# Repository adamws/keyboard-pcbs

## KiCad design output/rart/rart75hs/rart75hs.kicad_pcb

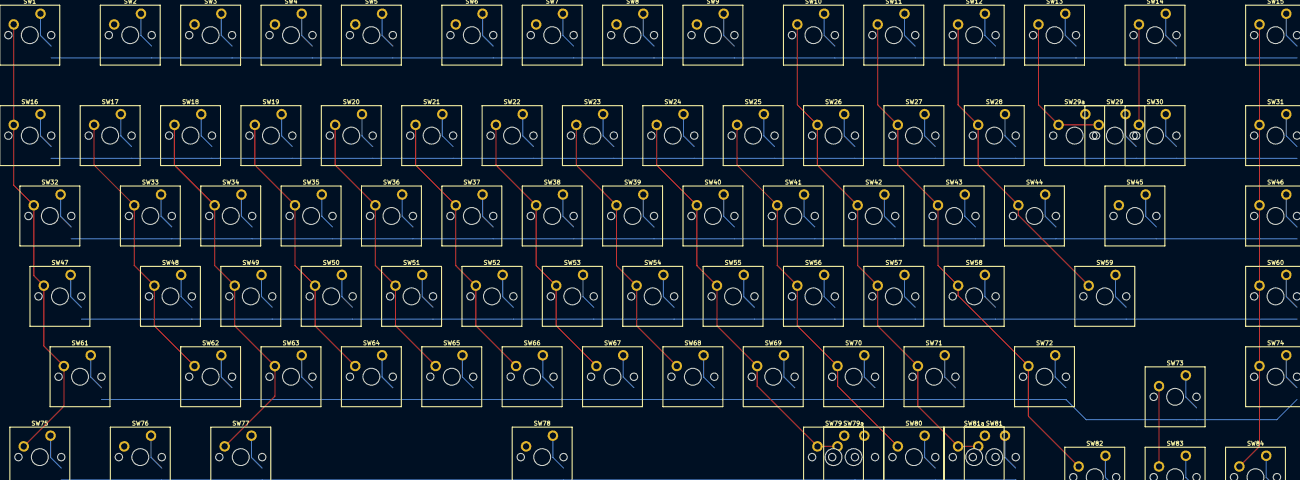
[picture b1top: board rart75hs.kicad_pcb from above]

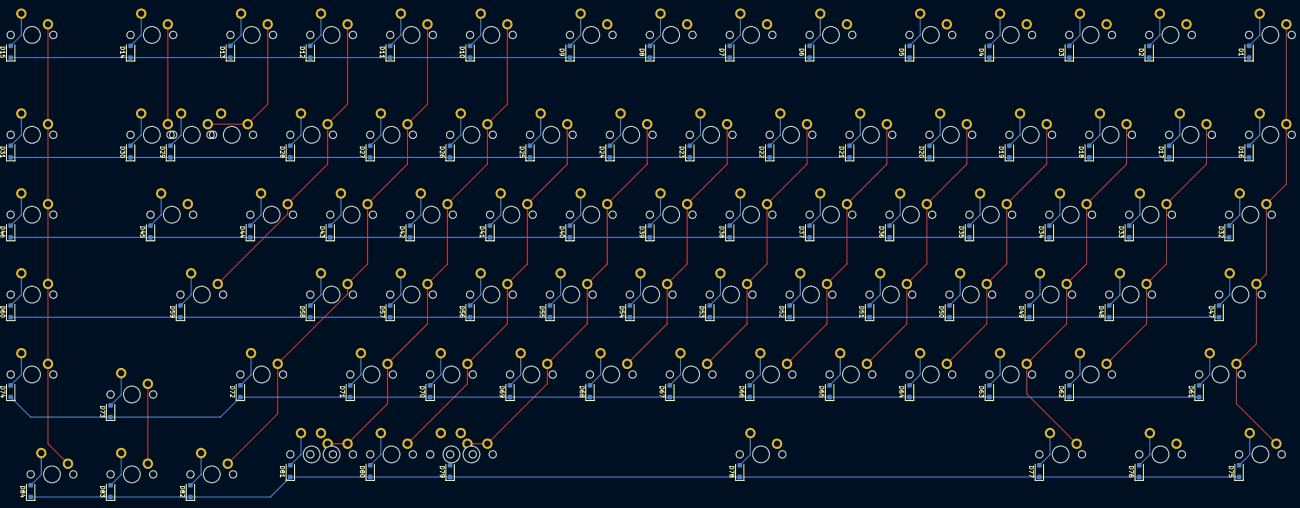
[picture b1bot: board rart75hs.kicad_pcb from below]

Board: 2 copper layers, 171 parts (84 on the bottom side), 106 nets.

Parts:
D1, D2, D3, D4, D5, D6, D7, D8, D9, D10, D11, D12, D13, D14, D15, D16, D17, D18, D19, D20, D21, D22, D23, D24, D25, D26, D27, D28, D29, D30, D31, D32, D33, D34, D35, D36, D37, D38, D39, D40, D41, D42, D43, D44, D45, D46, D47, D48, D49, D50, D51, D52, D53, D54, D55, D56, D57, D58, D59, D60, D61, D62, D63, D64, D65, D66, D67, D68, D69, D70, D71, D72, D73, D74, D75, D76, D77, D78, D79, D80, D81, D82, D83, D84: D_SOD-123F
SW1, SW2, SW3, SW4, SW5, SW6, SW7, SW8, SW9, SW10, SW11, SW12, SW13, SW14, SW15, SW16, SW17, SW18, SW19, SW20, SW21, SW22, SW23, SW24, SW25, SW26, SW27, SW28, SW29, SW29a, SW30, SW31, SW32, SW33, SW34, SW35, SW36, SW37, SW38, SW39, SW40, SW41, SW42, SW43, SW44, SW45, SW46, SW47, SW48, SW49, SW50, SW51, SW52, SW53, SW54, SW55, SW56, SW57, SW58, SW59, SW60, SW61, SW62, SW63, SW64, SW65, SW66, SW67, SW68, SW69, SW70, SW71, SW72, SW73, SW74, SW75, SW76, SW77, SW78, SW79, SW79a, SW80, SW81, SW81a, SW82, SW83, SW84: SW_Cherry_MX_PCB_1.00u

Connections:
COL0: SW1.1, SW16.1, SW32.1, SW47.1, SW61.1, SW75.1
COL1: SW2.1, SW17.1, SW33.1, SW48.1, SW62.1, SW76.1
COL2: SW3.1, SW18.1, SW34.1, SW49.1, SW63.1, SW77.1
COL3: SW4.1, SW19.1, SW35.1, SW50.1, SW64.1
COL4: SW5.1, SW20.1, SW36.1, SW51.1, SW65.1, SW78.1
COL5: SW6.1, SW21.1, SW37.1, SW52.1, SW66.1
COL6: SW7.1, SW22.1, SW38.1, SW53.1, SW67.1
COL7: SW8.1, SW23.1, SW39.1, SW54.1, SW68.1
COL8: SW9.1, SW24.1, SW40.1, SW55.1, SW69.1, SW79.1, SW79a.1
COL9: SW25.1, SW41.1, SW56.1, SW70.1, SW80.1
COL10: SW10.1, SW26.1, SW42.1, SW57.1, SW71.1, SW81.1, SW81a.1
COL11: SW11.1, SW27.1, SW43.1, SW58.1, SW72.1, SW82.1
COL12: SW12.1, SW28.1, SW44.1, SW59.1
COL13: SW13.1, SW29.1, SW29a.1, SW45.1
COL14: SW14.1, SW30.1, SW73.1, SW83.1
COL15: SW15.1, SW31.1, SW46.1, SW60.1, SW74.1, SW84.1
unnamed: D1.2, SW1.2
unnamed: D2.2, SW2.2
unnamed: D3.2, SW3.2
unnamed: D4.2, SW4.2
unnamed: D5.2, SW5.2
unnamed: D6.2, SW6.2
unnamed: D7.2, SW7.2
unnamed: D8.2, SW8.2
unnamed: D9.2, SW9.2
unnamed: D10.2, SW10.2
unnamed: D11.2, SW11.2
unnamed: D12.2, SW12.2
unnamed: D13.2, SW13.2
unnamed: D14.2, SW14.2
unnamed: D15.2, SW15.2
unnamed: D16.2, SW16.2
unnamed: D17.2, SW17.2
unnamed: D18.2, SW18.2
unnamed: D19.2, SW19.2
unnamed: D20.2, SW20.2
unnamed: D21.2, SW21.2
unnamed: D22.2, SW22.2
unnamed: D23.2, SW23.2
unnamed: D24.2, SW24.2
unnamed: D25.2, SW25.2
unnamed: D26.2, SW26.2
unnamed: D27.2, SW27.2
unnamed: D28.2, SW28.2
unnamed: D29.2, SW29.2, SW29a.2
unnamed: D30.2, SW30.2
unnamed: D31.2, SW31.2
unnamed: D32.2, SW32.2
unnamed: D33.2, SW33.2
unnamed: D34.2, SW34.2
unnamed: D35.2, SW35.2
unnamed: D36.2, SW36.2
unnamed: D37.2, SW37.2
unnamed: D38.2, SW38.2
unnamed: D39.2, SW39.2
unnamed: D40.2, SW40.2
unnamed: D41.2, SW41.2
unnamed: D42.2, SW42.2
unnamed: D43.2, SW43.2
unnamed: D44.2, SW44.2
unnamed: D45.2, SW45.2
unnamed: D46.2, SW46.2
unnamed: D47.2, SW47.2
unnamed: D48.2, SW48.2
unnamed: D49.2, SW49.2
unnamed: D50.2, SW50.2
unnamed: D51.2, SW51.2
unnamed: D52.2, SW52.2
unnamed: D53.2, SW53.2
unnamed: D54.2, SW54.2
unnamed: D55.2, SW55.2
unnamed: D56.2, SW56.2
unnamed: D57.2, SW57.2
unnamed: D58.2, SW58.2
unnamed: D59.2, SW59.2
unnamed: D60.2, SW60.2
unnamed: D61.2, SW61.2
unnamed: D62.2, SW62.2
unnamed: D63.2, SW63.2
unnamed: D64.2, SW64.2
unnamed: D65.2, SW65.2
unnamed: D66.2, SW66.2
unnamed: D67.2, SW67.2
unnamed: D68.2, SW68.2
unnamed: D69.2, SW69.2
unnamed: D70.2, SW70.2
unnamed: D71.2, SW71.2
unnamed: D72.2, SW72.2
unnamed: D73.2, SW73.2
unnamed: D74.2, SW74.2
unnamed: D75.2, SW75.2
unnamed: D76.2, SW76.2
unnamed: D77.2, SW77.2
unnamed: D78.2, SW78.2
unnamed: D79.2, SW79.2, SW79a.2
unnamed: D80.2, SW80.2
unnamed: D81.2, SW81.2, SW81a.2
unnamed: D82.2, SW82.2
unnamed: D83.2, SW83.2
unnamed: D84.2, SW84.2
ROW0: D1.1, D2.1, D3.1, D4.1, D5.1, D6.1, D7.1, D8.1, D9.1, D10.1, D11.1, D12.1, D13.1, D14.1, D15.1
ROW1: D16.1, D17.1, D18.1, D19.1, D20.1, D21.1, D22.1, D23.1, D24.1, D25.1, D26.1, D27.1, D28.1, D29.1, D30.1, D31.1
ROW2: D32.1, D33.1, D34.1, D35.1, D36.1, D37.1, D38.1, D39.1, D40.1, D41.1, D42.1, D43.1, D44.1, D45.1, D46.1
ROW3: D47.1, D48.1, D49.1, D50.1, D51.1, D52.1, D53.1, D54.1, D55.1, D56.1, D57.1, D58.1, D59.1, D60.1
ROW4: D61.1, D62.1, D63.1, D64.1, D65.1, D66.1, D67.1, D68.1, D69.1, D70.1, D71.1, D72.1, D73.1, D74.1
ROW5: D75.1, D76.1, D77.1, D78.1, D79.1, D80.1, D81.1, D82.1, D83.1, D84.1

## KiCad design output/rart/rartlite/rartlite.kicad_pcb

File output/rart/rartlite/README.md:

## rart/rartlite

[layout](rartlite-kle.json) - [PCB](rartlite.kicad_pcb)

{:loading="lazy"}

[Open in keyboard-layout-editor](http://www.keyboard-layout-editor.com/##@@=0,0%0A%0A%0A0,0&=1,0%0A%0A%0A0,0&=0,1%0A%0A%0A0,0&=1,1%0A%0A%0A0,0&=0,2%0A%0A%0A0,0&=1,2%0A%0A%0A0,0&=0,3%0A%0A%0A0,0&=1,3%0A%0A%0A0,0&=0,4%0A%0A%0A0,0&=1,4%0A%0A%0A0,0&=3,4%0A%0A%0A0,0&=0,5%0A%0A%0A0,0&_x:0.25;&=1,5%0A%0A%0A0,0&=0,6%0A%0A%0A0,0&=1,6%0A%0A%0A0,0;&@_w:1.5;&=2,0%0A%0A%0A0,0&=3,0%0A%0A%0A0,0&=2,1%0A%0A%0A0,0&=3,1%0A%0A%0A0,0&=2,2%0A%0A%0A0,0&=3,2%0A%0A%0A0,0&=2,3%0A%0A%0A0,0&=3,3%0A%0A%0A0,0&=2,4%0A%0A%0A0,0&=5,4%0A%0A%0A0,0&_w:1.5;&=2,5%0A%0A%0A0,0&_x:0.25;&=3,5%0A%0A%0A0,0&=2,6%0A%0A%0A0,0&=3,6%0A%0A%0A0,0;&@_w:1.75;&=4,0%0A%0A%0A0,0&=5,0%0A%0A%0A0,0&=4,1%0A%0A%0A0,0&=5,1%0A%0A%0A0,0&=4,2%0A%0A%0A0,0&=5,2%0A%0A%0A0,0&=4,3%0A%0A%0A0,0&=5,3%0A%0A%0A0,0&=4,4%0A%0A%0A0,0&=7,4%0A%0A%0A0,0&_x:1.5;&=5,5%0A%0A%0A0,0&=4,6%0A%0A%0A0,0&=5,6%0A%0A%0A0,0;&@_x:11&y:-0.75;&=4,5%0A%0A%0A0,0;&@_y:-0.25&w:1.25;&=6,0%0A%0A%0A0,0&=7,0%0A%0A%0A0,0&_w:2.25;&=6,1%0A%0A%0A0,0&_w:1.25;&=6,2%0A%0A%0A0,0&_w:2.75;&=6,3%0A%0A%0A0,0&_w:1.25;&=7,3%0A%0A%0A0,0&_x:3.5;&=6,6%0A%0A%0A0,0&=7,6%0A%0A%0A0,0;&@_x:10&y:-0.75;&=6,4%0A%0A%0A0,0&=6,5%0A%0A%0A0,0&=7,5%0A%0A%0A0,0;&@=0,0%0A%0A%0A0,1&=1,0%0A%0A%0A0,1&=0,1%0A%0A%0A0,1&=1,1%0A%0A%0A0,1&=0,2%0A%0A%0A0,1&=1,2%0A%0A%0A0,1&=0,3%0A%0A%0A0,1&=1,3%0A%0A%0A0,1&=0,4%0A%0A%0A0,1&=1,4%0A%0A%0A0,1&=3,4%0A%0A%0A0,1&=0,5%0A%0A%0A0,1&_x:0.25;&=1,5%0A%0A%0A0,1&=0,6%0A%0A%0A0,1&=1,6%0A%0A%0A0,1;&@_w:1.5;&=2,0%0A%0A%0A0,1&=3,0%0A%0A%0A0,1&=2,1%0A%0A%0A0,1&=3,1%0A%0A%0A0,1&=2,2%0A%0A%0A0,1&=3,2%0A%0A%0A0,1&=2,3%0A%0A%0A0,1&=3,3%0A%0A%0A0,1&=2,4%0A%0A%0A0,1&=5,4%0A%0A%0A0,1&_w:1.5;&=2,5%0A%0A%0A0,1&_x:0.25;&=3,5%0A%0A%0A0,1&=2,6%0A%0A%0A0,1&=3,6%0A%0A%0A0,1;&@_w:1.75;&=4,0%0A%0A%0A0,1&=5,0%0A%0A%0A0,1&=4,1%0A%0A%0A0,1&=5,1%0A%0A%0A0,1&=4,2%0A%0A%0A0,1&=5,2%0A%0A%0A0,1&=4,3%0A%0A%0A0,1&=5,3%0A%0A%0A0,1&=4,4%0A%0A%0A0,1&=7,4%0A%0A%0A0,1&_x:1.5;&=5,5%0A%0A%0A0,1&=4,6%0A%0A%0A0,1&=5,6%0A%0A%0A0,1;&@_x:11&y:-0.75;&=4,5%0A%0A%0A0,1;&@_y:-0.25&w:1.25;&=6,0%0A%0A%0A0,1&=7,0%0A%0A%0A0,1&_w:6.25;&=6,2%0A%0A%0A0,1&_w:1.25;&=7,3%0A%0A%0A0,1&_x:3.5;&=6,6%0A%0A%0A0,1&=7,6%0A%0A%0A0,1;&@_x:10&y:-0.75;&=6,4%0A%0A%0A0,1&=6,5%0A%0A%0A0,1&=7,5%0A%0A%0A0,1;&@=1,6%0A%0A%0A0,2&=0,6%0A%0A%0A0,2&=1,5%0A%0A%0A0,2&_x:0.25;&=0,5%0A%0A%0A0,2&=3,4%0A%0A%0A0,2&=1,4%0A%0A%0A0,2&=0,4%0A%0A%0A0,2&=1,3%0A%0A%0A0,2&=0,3%0A%0A%0A0,2&=1,2%0A%0A%0A0,2&=0,2%0A%0A%0A0,2&=1,1%0A%0A%0A0,2&=0,1%0A%0A%0A0,2&=1,0%0A%0A%0A0,2&=0,0%0A%0A%0A0,2;&@=3,6%0A%0A%0A0,2&=2,6%0A%0A%0A0,2&=3,5%0A%0A%0A0,2&_x:0.25&w:1.5;&=2,5%0A%0A%0A0,2&=5,4%0A%0A%0A0,2&=2,4%0A%0A%0A0,2&=3,3%0A%0A%0A0,2&=2,3%0A%0A%0A0,2&=3,2%0A%0A%0A0,2&=2,2%0A%0A%0A0,2&=3,1%0A%0A%0A0,2&=2,1%0A%0A%0A0,2&=3,0%0A%0A%0A0,2&_w:1.5;&=2,0%0A%0A%0A0,2;&@=5,6%0A%0A%0A0,2&=4,6%0A%0A%0A0,2&=5,5%0A%0A%0A0,2&_x:1.5;&=7,4%0A%0A%0A0,2&=4,4%0A%0A%0A0,2&=5,3%0A%0A%0A0,2&=4,3%0A%0A%0A0,2&=5,2%0A%0A%0A0,2&=4,2%0A%0A%0A0,2&=5,1%0A%0A%0A0,2&=4,1%0A%0A%0A0,2&=5,0%0A%0A%0A0,2&_w:1.75;&=4,0%0A%0A%0A0,2;&@_x:3.25&y:-0.75;&=4,5%0A%0A%0A0,2;&@_y:-0.25;&=7,6%0A%0A%0A0,2&=6,6%0A%0A%0A0,2&_x:3.5&w:1.25;&=7,3%0A%0A%0A0,2&_w:2.75;&=6,3%0A%0A%0A0,2&_w:1.25;&=6,2%0A%0A%0A0,2&_w:2.25;&=6,1%0A%0A%0A0,2&=7,0%0A%0A%0A0,2&_w:1.25;&=6,0%0A%0A%0A0,2;&@_x:2.25&y:-0.75;&=7,5%0A%0A%0A0,2&=6,5%0A%0A%0A0,2&=6,4%0A%0A%0A0,2;&@=1,6%0A%0A%0A0,3&=0,6%0A%0A%0A0,3&=1,5%0A%0A%0A0,3&_x:0.25;&=0,5%0A%0A%0A0,3&=3,4%0A%0A%0A0,3&=1,4%0A%0A%0A0,3&=0,4%0A%0A%0A0,3&=1,3%0A%0A%0A0,3&=0,3%0A%0A%0A0,3&=1,2%0A%0A%0A0,3&=0,2%0A%0A%0A0,3&=1,1%0A%0A%0A0,3&=0,1%0A%0A%0A0,3&=1,0%0A%0A%0A0,3&=0,0%0A%0A%0A0,3;&@=3,6%0A%0A%0A0,3&=2,6%0A%0A%0A0,3&=3,5%0A%0A%0A0,3&_x:0.25&w:1.5;&=2,5%0A%0A%0A0,3&=5,4%0A%0A%0A0,3&=2,4%0A%0A%0A0,3&=3,3%0A%0A%0A0,3&=2,3%0A%0A%0A0,3&=3,2%0A%0A%0A0,3&=2,2%0A%0A%0A0,3&=3,1%0A%0A%0A0,3&=2,1%0A%0A%0A0,3&=3,0%0A%0A%0A0,3&_w:1.5;&=2,0%0A%0A%0A0,3;&@=5,6%0A%0A%0A0,3&=4,6%0A%0A%0A0,3&=5,5%0A%0A%0A0,3&_x:1.5;&=7,4%0A%0A%0A0,3&=4,4%0A%0A%0A0,3&=5,3%0A%0A%0A0,3&=4,3%0A%0A%0A0,3&=5,2%0A%0A%0A0,3&=4,2%0A%0A%0A0,3&=5,1%0A%0A%0A0,3&=4,1%0A%0A%0A0,3&=5,0%0A%0A%0A0,3&_w:1.75;&=4,0%0A%0A%0A0,3;&@_x:3.25&y:-0.75;&=4,5%0A%0A%0A0,3;&@_y:-0.25;&=7,6%0A%0A%0A0,3&=6,6%0A%0A%0A0,3&_x:3.5&w:1.25;&=7,3%0A%0A%0A0,3&_w:6.25;&=6,2%0A%0A%0A0,3&=7,0%0A%0A%0A0,3&_w:1.25;&=6,0%0A%0A%0A0,3;&@_x:2.25&y:-0.75;&=7,5%0A%0A%0A0,3&=6,5%0A%0A%0A0,3&=6,4%0A%0A%0A0,3)

{:loading="lazy"}

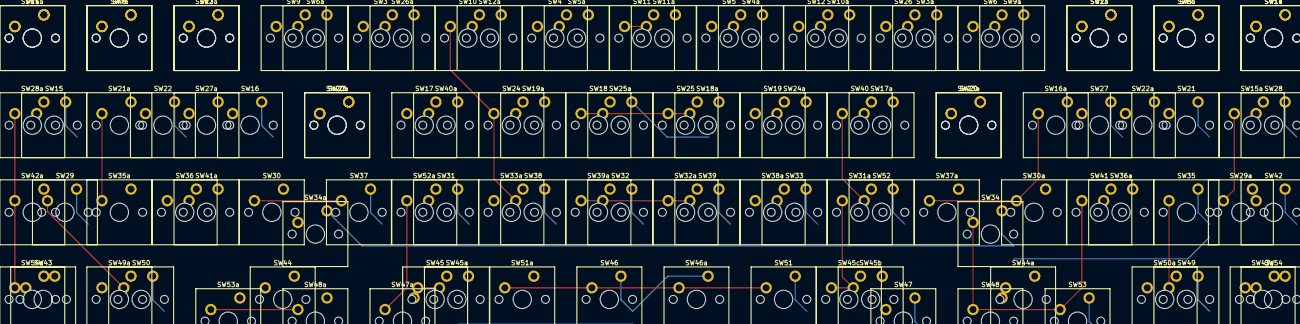
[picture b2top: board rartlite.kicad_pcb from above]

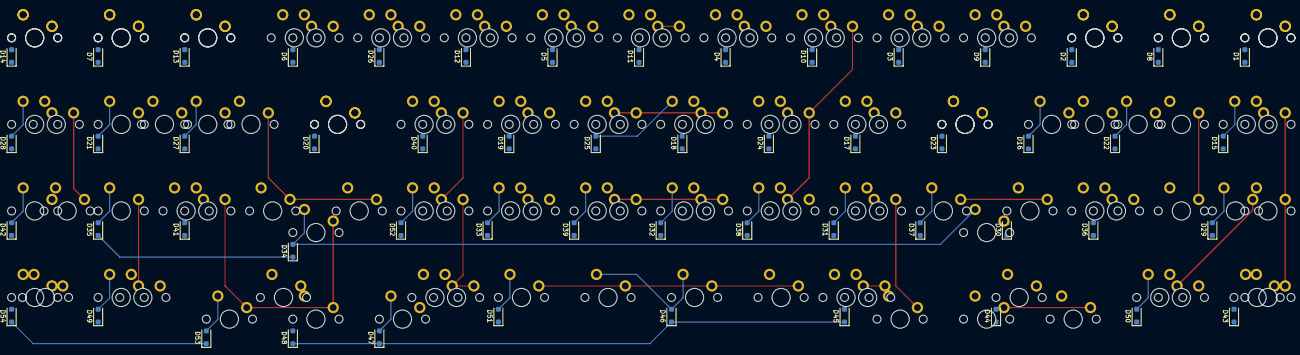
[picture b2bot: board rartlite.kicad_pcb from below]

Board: 2 copper layers, 164 parts (54 on the bottom side), 69 nets.

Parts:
D1, D2, D3, D4, D5, D6, D7, D8, D9, D10, D11, D12, D13, D14, D15, D16, D17, D18, D19, D20, D21, D22, D23, D24, D25, D26, D27, D28, D29, D30, D31, D32, D33, D34, D35, D36, D37, D38, D39, D40, D41, D42, D43, D44, D45, D46, D47, D48, D49, D50, D51, D52, D53, D54: D_SOD-123F
SW1, SW1a, SW2, SW2a, SW3, SW3a, SW4, SW4a, SW5, SW5a, SW6, SW6a, SW7, SW7a, SW8, SW8a, SW9, SW9a, SW10, SW10a, SW11, SW11a, SW12, SW12a, SW13, SW13a, SW14, SW14a, SW15, SW15a, SW16, SW16a, SW17, SW17a, SW18, SW18a, SW19, SW19a, SW20, SW20a, SW21, SW21a, SW22, SW22a, SW23, SW23a, SW24, SW24a, SW25, SW25a, SW26, SW26a, SW27, SW27a, SW28, SW28a, SW29, SW29a, SW30, SW30a, SW31, SW31a, SW32, SW32a, SW33, SW33a, SW34, SW34a, SW35, SW35a, SW36, SW36a, SW37, SW37a, SW38, SW38a, SW39, SW39a, SW40, SW40a, SW41, SW41a, SW42, SW42a, SW43, SW43a, SW44, SW44a, SW45, SW45a, SW45b, SW45c, SW46, SW46a, SW47, SW47a, SW48, SW48a, SW49, SW49a, SW50, SW50a, SW51, SW51a, SW52, SW52a, SW53, SW53a, SW54, SW54a: SW_Cherry_MX_PCB_1.00u

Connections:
COL0: SW1.1, SW1a.1, SW8.1, SW8a.1, SW15.1, SW15a.1, SW22.1, SW22a.1, SW29.1, SW29a.1, SW36.1, SW36a.1, SW43.1, SW43a.1, SW50.1, SW50a.1
COL1: SW2.1, SW2a.1, SW9.1, SW9a.1, SW16.1, SW16a.1, SW23.1, SW23a.1, SW30.1, SW30a.1, SW37.1, SW37a.1, SW44.1, SW44a.1
COL2: SW3.1, SW3a.1, SW10.1, SW10a.1, SW17.1, SW17a.1, SW24.1, SW24a.1, SW31.1, SW31a.1, SW38.1, SW38a.1, SW45.1, SW45a.1, SW45b.1, SW45c.1
COL3: SW4.1, SW4a.1, SW11.1, SW11a.1, SW18.1, SW18a.1, SW25.1, SW25a.1, SW32.1, SW32a.1, SW39.1, SW39a.1, SW46.1, SW46a.1, SW51.1, SW51a.1
COL4: SW5.1, SW5a.1, SW12.1, SW12a.1, SW19.1, SW19a.1, SW26.1, SW26a.1, SW33.1, SW33a.1, SW40.1, SW40a.1, SW47.1, SW47a.1, SW52.1, SW52a.1
COL5: SW6.1, SW6a.1, SW13.1, SW13a.1, SW20.1, SW20a.1, SW27.1, SW27a.1, SW34.1, SW34a.1, SW41.1, SW41a.1, SW48.1, SW48a.1, SW53.1, SW53a.1
COL6: SW7.1, SW7a.1, SW14.1, SW14a.1, SW21.1, SW21a.1, SW28.1, SW28a.1, SW35.1, SW35a.1, SW42.1, SW42a.1, SW49.1, SW49a.1, SW54.1, SW54a.1
unnamed: D1.2, SW1.2, SW1a.2
unnamed: D2.2, SW2.2, SW2a.2
unnamed: D3.2, SW3.2, SW3a.2
unnamed: D4.2, SW4.2, SW4a.2
unnamed: D5.2, SW5.2, SW5a.2
unnamed: D6.2, SW6.2, SW6a.2
unnamed: D7.2, SW7.2, SW7a.2
unnamed: D8.2, SW8.2, SW8a.2
unnamed: D9.2, SW9.2, SW9a.2
unnamed: D10.2, SW10.2, SW10a.2
unnamed: D11.2, SW11.2, SW11a.2
unnamed: D12.2, SW12.2, SW12a.2
unnamed: D13.2, SW13.2, SW13a.2
unnamed: D14.2, SW14.2, SW14a.2
unnamed: D15.2, SW15.2, SW15a.2
unnamed: D16.2, SW16.2, SW16a.2
unnamed: D17.2, SW17.2, SW17a.2
unnamed: D18.2, SW18.2, SW18a.2
unnamed: D19.2, SW19.2, SW19a.2
unnamed: D20.2, SW20.2, SW20a.2
unnamed: D21.2, SW21.2, SW21a.2
unnamed: D22.2, SW22.2, SW22a.2
unnamed: D23.2, SW23.2, SW23a.2
unnamed: D24.2, SW24.2, SW24a.2
unnamed: D25.2, SW25.2, SW25a.2
unnamed: D26.2, SW26.2, SW26a.2
unnamed: D27.2, SW27.2, SW27a.2
unnamed: D28.2, SW28.2, SW28a.2
unnamed: D29.2, SW29.2, SW29a.2
unnamed: D30.2, SW30.2, SW30a.2
unnamed: D31.2, SW31.2, SW31a.2
unnamed: D32.2, SW32.2, SW32a.2
unnamed: D33.2, SW33.2, SW33a.2
unnamed: D34.2, SW34.2, SW34a.2
unnamed: D35.2, SW35.2, SW35a.2
unnamed: D36.2, SW36.2, SW36a.2
unnamed: D37.2, SW37.2, SW37a.2
unnamed: D38.2, SW38.2, SW38a.2
unnamed: D39.2, SW39.2, SW39a.2
unnamed: D40.2, SW40.2, SW40a.2
unnamed: D41.2, SW41.2, SW41a.2
unnamed: D42.2, SW42.2, SW42a.2
unnamed: D43.2, SW43.2, SW43a.2
unnamed: D44.2, SW44.2, SW44a.2
unnamed: D45.2, SW45.2, SW45a.2, SW45b.2, SW45c.2
unnamed: D46.2, SW46.2, SW46a.2
unnamed: D47.2, SW47.2, SW47a.2
unnamed: D48.2, SW48.2, SW48a.2
unnamed: D49.2, SW49.2, SW49a.2
unnamed: D50.2, SW50.2, SW50a.2
unnamed: D51.2, SW51.2, SW51a.2
unnamed: D52.2, SW52.2, SW52a.2
unnamed: D53.2, SW53.2, SW53a.2
unnamed: D54.2, SW54.2, SW54a.2
ROW0: D1.1, D2.1, D3.1, D4.1, D5.1, D6.1, D7.1
ROW1: D8.1, D9.1, D10.1, D11.1, D12.1, D13.1, D14.1
ROW2: D15.1, D16.1, D17.1, D18.1, D19.1, D20.1, D21.1
ROW3: D22.1, D23.1, D24.1, D25.1, D26.1, D27.1, D28.1
ROW4: D29.1, D30.1, D31.1, D32.1, D33.1, D34.1, D35.1
ROW5: D36.1, D37.1, D38.1, D39.1, D40.1, D41.1, D42.1
ROW6: D43.1, D44.1, D45.1, D46.1, D47.1, D48.1, D49.1
ROW7: D50.1, D51.1, D52.1, D53.1, D54.1
